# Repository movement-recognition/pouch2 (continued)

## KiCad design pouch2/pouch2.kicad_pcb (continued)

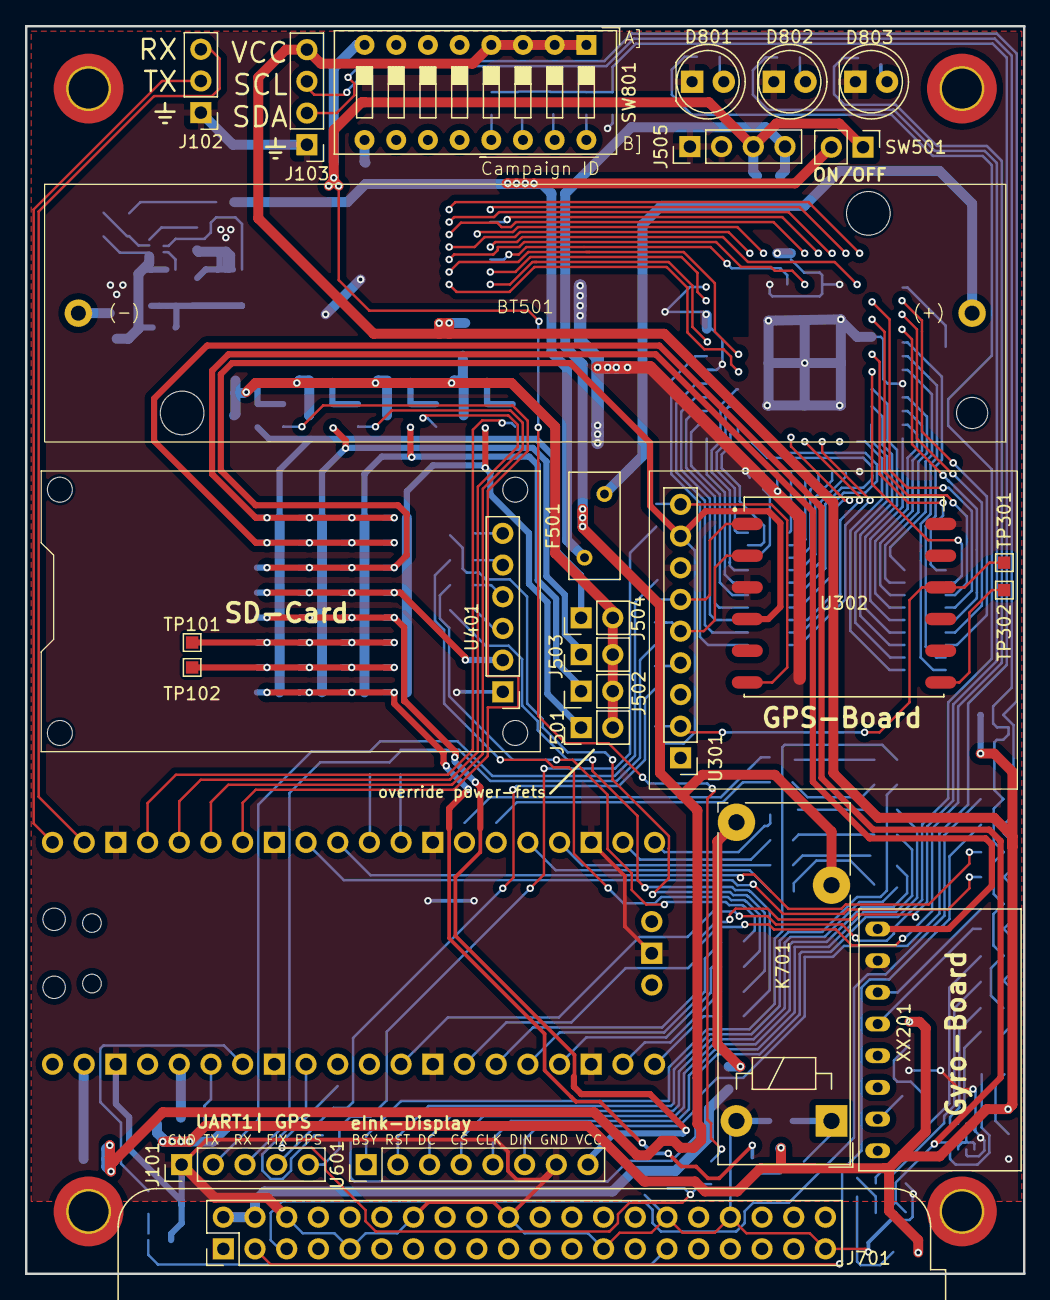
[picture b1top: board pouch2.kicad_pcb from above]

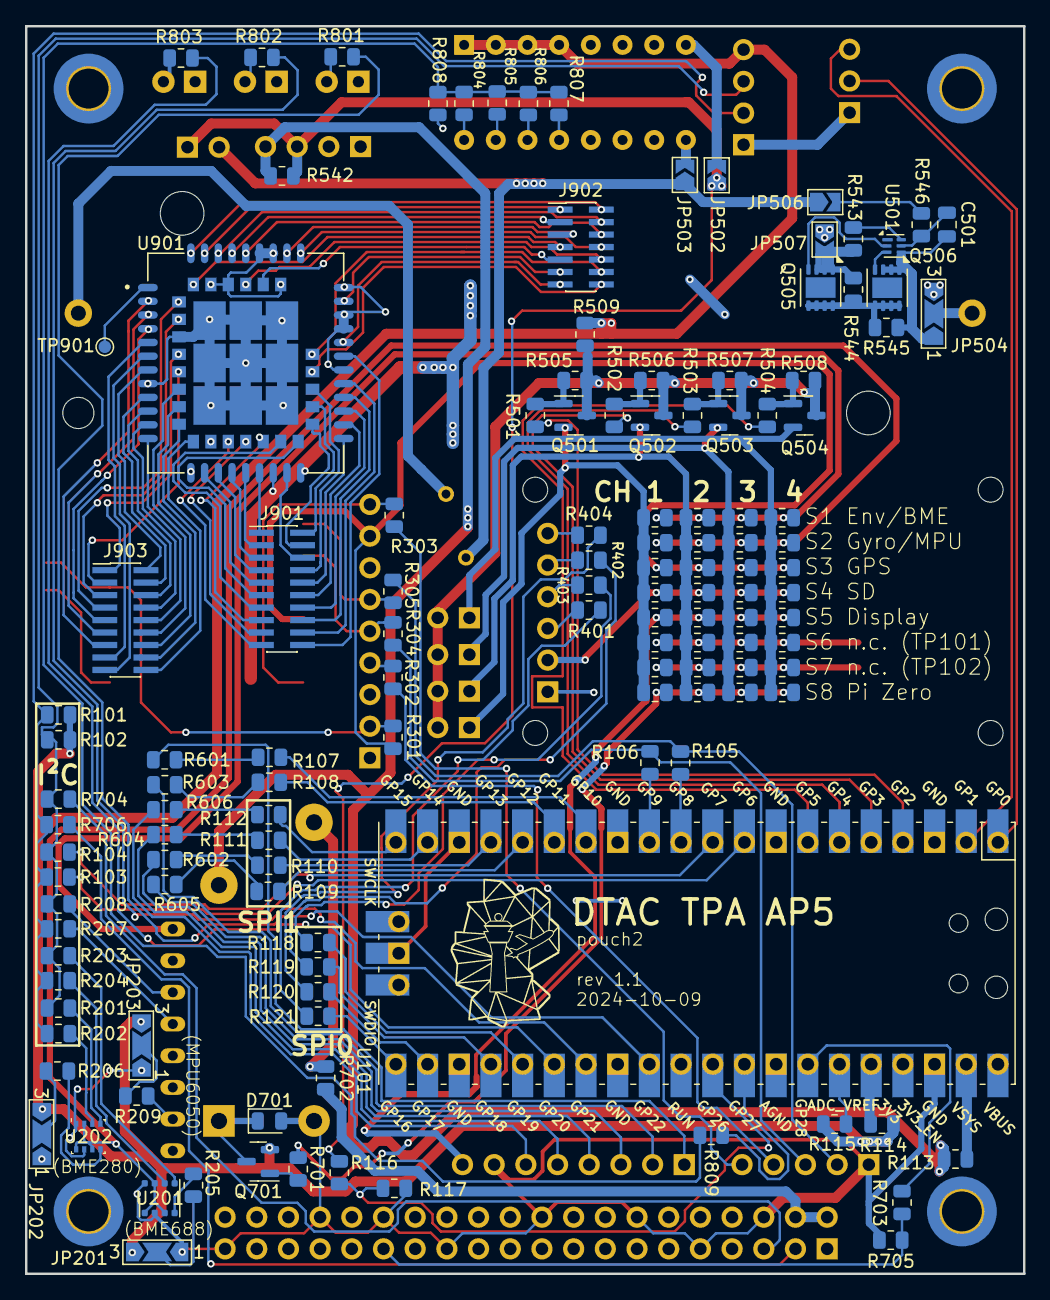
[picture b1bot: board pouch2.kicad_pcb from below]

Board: 2 copper layers, 80.0 x 100.0 mm, 162 parts (132 on the bottom side), 175 nets.

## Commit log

2024-08-31 initial setup
2024-09-01 added power, sdcard
2024-09-01 updated submodule
2024-09-05 added pi zero header
2024-09-08 started PCB design
2024-09-08 PCB and footprint arrangements
2024-09-11 updated backside of PCB
2024-09-12 minor updates
2024-09-13 added SIM 868 footprints
2024-09-14 added SIM 868 schematic
2024-09-14 started routing
2024-09-14 drawed a lot of things
2024-09-15 finished first routing pass
2024-09-22 updated power routing
2024-09-24 added sim-module breakout
2024-10-07 added VCC-battery measurement line
2024-10-09 rev1
2024-10-09 moved all holes on pads away
2024-10-09 rename pouch2 folder into pcb
2024-10-09 removed pouch folder (duplicate)
2024-10-09 added gitmodules-file
2024-10-09 chore: cleanup repo
2024-10-12 added pico-sdk as submodule
2024-10-12 initialized hardware documentation
2024-10-12 intermediate toolchain-setup docs
2024-10-12 intermediate toolchain-setup
2024-10-12 added free-rtos
2024-10-12 switched branch
2024-10-12 added wifi-scan and demo-processes
2024-10-13 extended docs
2024-10-29 added initial version of device comparison
2024-10-30 added colors and expanded description texts
2024-10-30 added colors and expanded description texts (II)
2024-10-30 updated GPIO pinout table
2024-10-30 added build scripts
2024-10-30 added basic architecture
2024-10-30 updated i2c-library
2024-10-30 added mpu6050-implementation
2024-10-30 improved mpu6050 initial configuration
2024-10-31 fixed duplicate variable names
2024-11-02 multicore test
2024-11-02 added tasker
2024-11-02 added vscode-settings
2024-11-02 added gitignore
2024-11-02 adde SimAcceleration
2024-11-02 updated PouchTasker
2024-11-02 added queue-logic to tasker
2024-11-11 extended specifications
2024-11-11 added lab scripts
2024-11-11 added BME280-library
2024-11-11 extended environmental lib
2024-11-11 fix mpu6050-conversion
2024-11-12 fixed lockup during I2c read
2024-11-13 added timing improvements for IMU, ENV
2024-11-18 fixed BME280 readings
2024-11-18 added spi-sdcard-library
2024-11-20 added tflite docs
2024-11-21 buildable code for sd-card, version 1
2024-11-21 remove no-OS-FatFS-SD-SDIO-SPI-RPi-Pico-package
2024-11-21 added new sd-card library
2024-11-26 fixed missing GND-line to SD-Card-Adapter
2024-11-26 added capacitor for SD-Card
2024-11-26 added details on SPI-Failure
2024-11-27 added queue, fixed SD-Card
2024-11-27 added IMU logging
2024-11-27 temporary gps debugging
2024-12-01 updated ToDos in PCB design
2024-12-01 added GPS library
2024-12-01 intermediate with custom GPS library
2024-12-06 update GPS parser
2024-12-06 fix CI
2024-12-06 embedded GPS into main and pouch tasker
